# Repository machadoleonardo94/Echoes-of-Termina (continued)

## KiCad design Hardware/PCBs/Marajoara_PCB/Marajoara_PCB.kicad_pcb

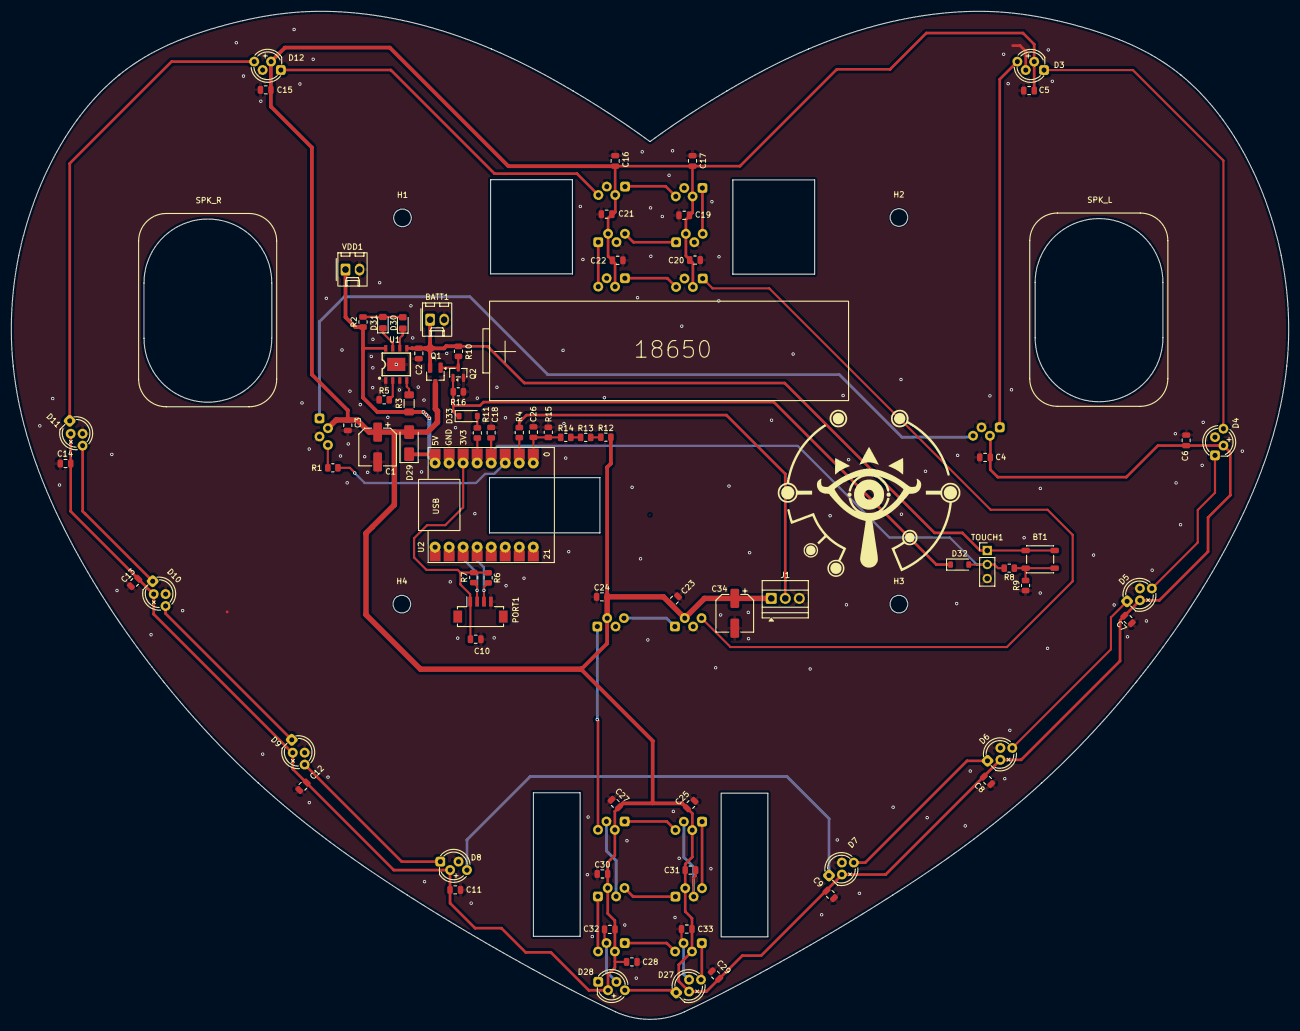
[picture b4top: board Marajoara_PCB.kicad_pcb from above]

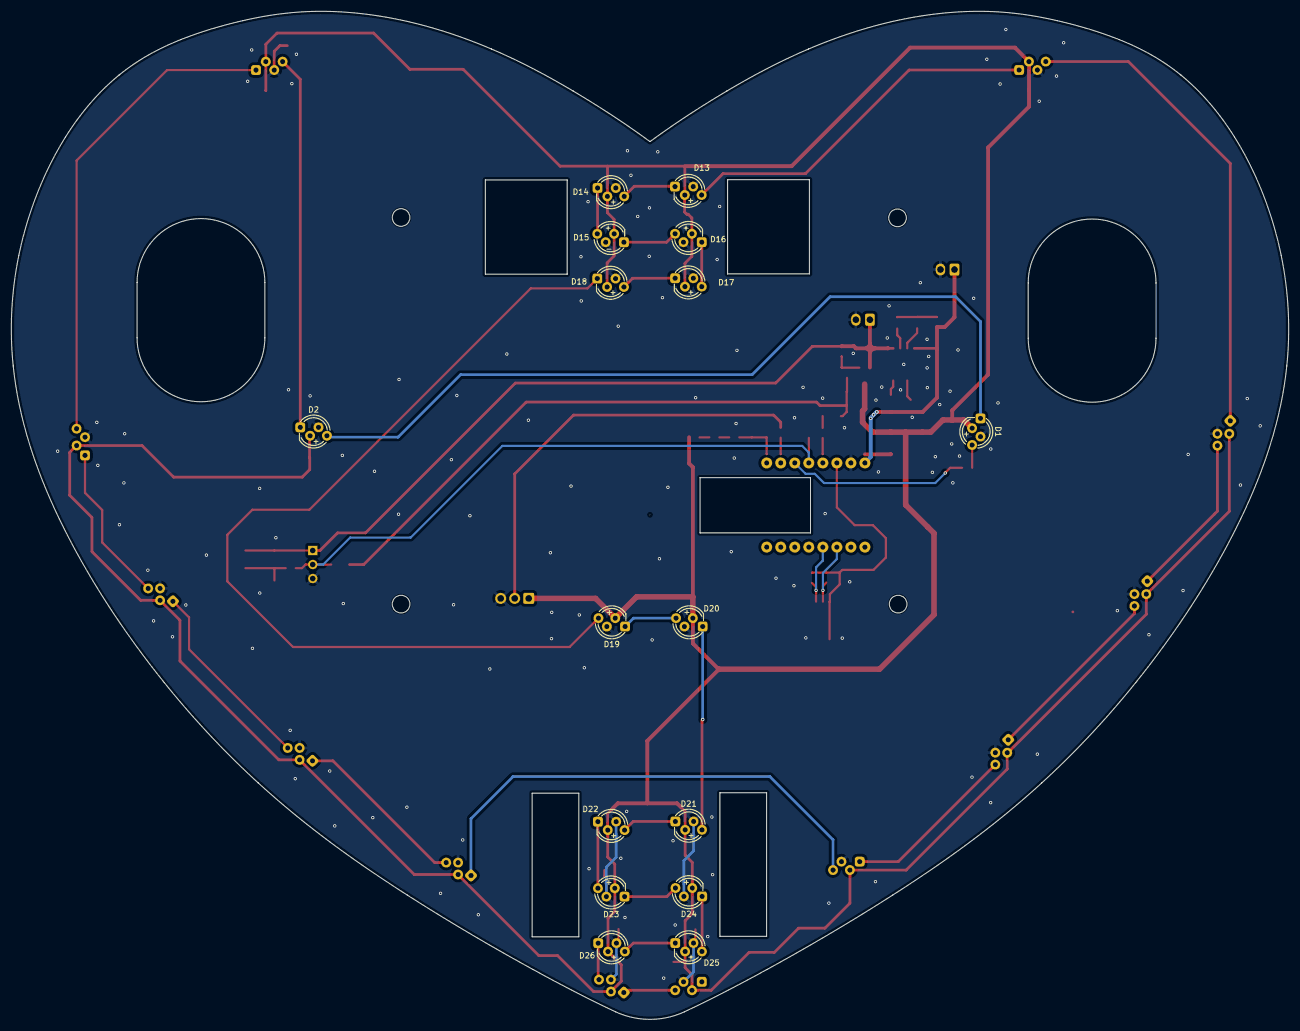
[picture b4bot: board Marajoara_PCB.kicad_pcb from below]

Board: 2 copper layers, 231.3 x 182.5 mm, 99 parts (16 on the bottom side), 52 nets.

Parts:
BATT1: Conn_01x02_Socket; Molex_KK-254_AE-6410-02A_1x02_P2.54mm_Vertical
BT1: SW_Push; SW_SPST_PTS647_Sx38
C1, C34: 220uF; CP_Elec_6.3x7.7
C2, C10: 10u; C_0805_2012Metric
C3, C4, C5, C6, C7, C8, C9, C11, C12, C13, C14, C15, C16, C17, C18, C19, C20, C21, C22, C23, C24, C25, C26, C27, C28, C29, C30, C31, C32, C33: 100nF; C_0805_2012Metric
D1, D2, D3, D4, D5, D6, D7, D8, D9, D10, D11, D12, D13, D14, D15, D16, D17, D18, D19, D20, D21, D22, D23, D24, D25, D26, D27, D28: WS2812B; WS2812B_PTH_staggered
D29: SS14; D_SMA
D30: LED_BLUE; LED_0805_2012Metric_Pad1.15x1.40mm_HandSolder
D31: LED_RED; LED_0805_2012Metric_Pad1.15x1.40mm_HandSolder
D32, D33: 1N4148W; D_SOD-123
H1, H2, H3, H4: MountingHole; MountingHole_3.2mm_M3
J1: Conn_01x03_Socket; TerminalBlock_Xinya_XY308-2.54-3P_1x03_P2.54mm_Horizontal
PORT1: Conn_01x04_Socket; Hirose_DF13C_CL535-0404-8-51_1x04-1MP_P1.25mm_Vertical
Q1: XR5P04; SOT-23_Handsoldering
Q2: 2N7002K; SOT-23
R1, R4, R11: 330; R_0805_2012Metric
R2, R5, R6, R7, R8: 2.2k; R_0805_2012Metric
R3: 220mR 1W 1%; R_1206_3216Metric_Pad1.30x1.75mm_HandSolder
R9, R10, R12, R13, R14, R15: 100k; R_0805_2012Metric
R16: 10k; R_0805_2012Metric
SPK_L: Speaker_4R_3W_35x25mm
SPK_R: Speaker_4R_3W_35x25mm
TOUCH1: Conn_01x03_Socket; PinHeader_1x03_P2.54mm_Vertical
U1: TP4056; ESOP-8_L4.9-W3.9-P1.27-LS6.0-BL-EP
U2: ESP32-C3-Supermini
VDD1: Conn_01x02_Socket; Molex_KK-254_AE-6410-02A_1x02_P2.54mm_Vertical

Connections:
+3.3V: C10.1, PORT1.1, R6.1, R7.1, U2.14 (3V3)
+5V: D29.1 (K), R2.1, R3.1, U1.8 (CE), U2.16 (5V), VDD1.1
+BATT: BATT1.1, BT1.1, C2.1, Q1.2 (S), R10.2, TOUCH1.1, U1.5 (BAT)
ADC1_0: C26.2, R14.1, R15.1, U2.9 (GPIO0)
Button_GPIO: C18.2, D32.2 (A), R8.2, TOUCH1.2, U2.12 (GPIO3)
GND: BATT1.2, C1.2, C2.2, C3.1, C4.1, C5.1, C6.1, C7.1, C8.1, C9.1, C10.2, C11.1, C12.1, C13.1, C14.1, C15.1, C16.1, C17.1, C18.1, C19.1, C20.1, C21.1, C22.1, C23.1, C24.1, C25.1, C26.1, C27.1, C28.1, C29.1, C30.1, C31.1, C32.1, C33.1, C34.2, D1.2 (VSS), D2.2 (VSS), D3.2 (VSS), D4.2 (VSS), D5.2 (VSS), D6.2 (VSS), D7.2 (VSS), D8.2 (VSS), D9.2 (VSS), D10.2 (VSS), D11.2 (VSS), D12.2 (VSS), D13.2 (VSS), D14.2 (VSS), D15.2 (VSS), D16.2 (VSS), D17.2 (VSS), D18.2 (VSS), D19.2 (VSS), D20.2 (VSS), D21.2 (VSS), D22.2 (VSS), D23.2 (VSS), D24.2 (VSS), D25.2 (VSS), D26.2 (VSS), D27.2 (VSS), D28.2 (VSS), J1.3, PORT1.4, Q2.2 (S), R5.1, R9.1, R15.2, R16.2, TOUCH1.3, U1.1 (TEMP), U1.3 (GND), U1.9 (EP), U2.15 (GND), VDD1.2
Majora_out: R1.1, U2.11 (GPIO2)
unnamed: BT1.2, R8.1, R9.2
unnamed: D1.1 (DIN), R1.2
unnamed: D1.4 (DOUT), D2.1 (DIN)
unnamed: D2.4 (DOUT), D3.1 (DIN)
unnamed: D3.4 (DOUT), D4.1 (DIN)
unnamed: D4.4 (DOUT), D5.1 (DIN)
unnamed: D5.4 (DOUT), D6.1 (DIN)
unnamed: D6.4 (DOUT), D7.1 (DIN)
unnamed: D7.4 (DOUT), D8.1 (DIN)
unnamed: D8.4 (DOUT), D9.1 (DIN)
unnamed: D9.4 (DOUT), D10.1 (DIN)
unnamed: D10.4 (DOUT), D11.1 (DIN)
unnamed: D11.4 (DOUT), D12.1 (DIN)
unnamed: D12.4 (DOUT), D13.1 (DIN)
unnamed: D13.4 (DOUT), D14.1 (DIN)
unnamed: D14.4 (DOUT), D15.1 (DIN)
unnamed: D15.4 (DOUT), D16.1 (DIN)
unnamed: D16.4 (DOUT), D17.1 (DIN)
unnamed: D17.4 (DOUT), D18.1 (DIN)
unnamed: D18.4 (DOUT), D19.1 (DIN)
unnamed: D19.4 (DOUT), D20.1 (DIN)
unnamed: D20.4 (DOUT), D21.1 (DIN)
unnamed: D21.4 (DOUT), D22.1 (DIN)
unnamed: D22.4 (DOUT), D23.1 (DIN)
unnamed: D23.4 (DOUT), D24.1 (DIN)
unnamed: D24.4 (DOUT), D25.1 (DIN)
unnamed: D25.4 (DOUT), D26.1 (DIN)
unnamed: D26.4 (DOUT), D27.1 (DIN)
unnamed: D27.4 (DOUT), D28.1 (DIN)
unnamed: D30.2 (A), D31.2 (A), R2.2
unnamed: D30.1 (K), U1.6 (STDBY#)
unnamed: D31.1 (K), U1.7 (CHRG#)
unnamed: D32.1 (K), D33.1 (K), Q2.1 (G), R16.1
unnamed: D33.2 (A), R11.2
unnamed: J1.2, R4.2
unnamed: Q1.1 (G), Q2.3 (D), R10.1
unnamed: R12.1, R13.2
unnamed: R13.1, R14.2
unnamed: R5.2, U1.2 (PROG)
unnamed: R3.2, U1.4 (VCC)
SCL: PORT1.3, R6.2, U2.4 (GPIO8)
SDA: PORT1.2, R7.2, U2.3 (GPIO7)
Strip_out: R4.1, U2.10 (GPIO1)
V_REG: C1.1, C3.2, C4.2, C5.2, C6.2, C7.2, C8.2, C9.2, C11.2, C12.2, C13.2, C14.2, C15.2, C16.2, C17.2, C19.2, C20.2, C21.2, C22.2, C23.2, C24.2, C25.2, C27.2, C28.2, C29.2, C30.2, C31.2, C32.2, C33.2, C34.1, D1.3 (VDD), D2.3 (VDD), D3.3 (VDD), D4.3 (VDD), D5.3 (VDD), D6.3 (VDD), D7.3 (VDD), D8.3 (VDD), D9.3 (VDD), D10.3 (VDD), D11.3 (VDD), D12.3 (VDD), D13.3 (VDD), D14.3 (VDD), D15.3 (VDD), D16.3 (VDD), D17.3 (VDD), D18.3 (VDD), D19.3 (VDD), D20.3 (VDD), D21.3 (VDD), D22.3 (VDD), D23.3 (VDD), D24.3 (VDD), D25.3 (VDD), D26.3 (VDD), D27.3 (VDD), D28.3 (VDD), D29.2 (A), J1.1, Q1.3 (D), R12.2
latch_enable: R11.1, U2.13 (GPIO4)

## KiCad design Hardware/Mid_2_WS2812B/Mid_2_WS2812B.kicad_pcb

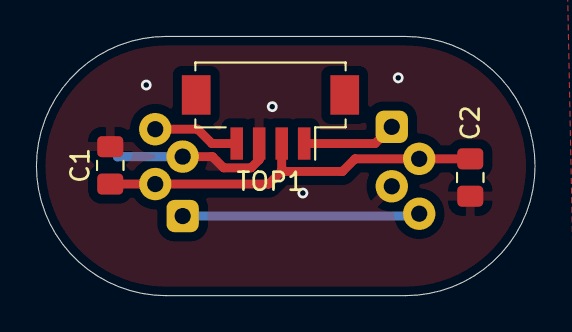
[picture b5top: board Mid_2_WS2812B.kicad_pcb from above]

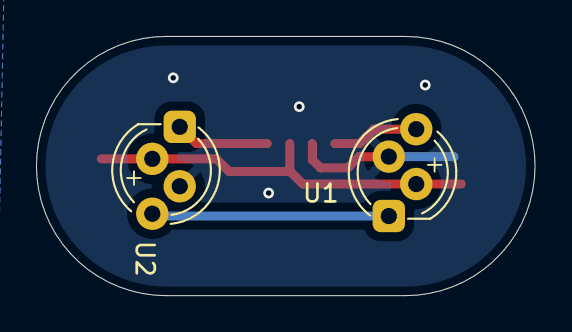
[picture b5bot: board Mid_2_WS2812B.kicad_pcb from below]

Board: 2 copper layers, 27.7 x 14.4 mm, 5 parts (2 on the bottom side), 5 nets.

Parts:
C1, C2: 100n; C_0805_2012Metric_Pad1.18x1.45mm_HandSolder
TOP1: Conn_01x04_Socket; Hirose_DF13C_CL535-0404-8-51_1x04-1MP_P1.25mm_Vertical
U1, U2: WS2812B; WS2812B_PTH_staggered

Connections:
GND: C1.2, C2.2, TOP1.3, U1.2 (VSS), U2.2 (VSS)
unnamed: U1.4 (DOUT), U2.1 (DIN)
Strip_in: TOP1.4, U1.1 (DIN)
Strip_out: TOP1.1, U2.4 (DOUT)
VCC: C1.1, C2.1, TOP1.2, U1.3 (VDD), U2.3 (VDD)

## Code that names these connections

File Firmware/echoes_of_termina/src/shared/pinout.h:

#ifndef PROJECT_GLOBAL_PINOUT
#define PROJECT_GLOBAL_PINOUT

#include "shared/dependencies.h"

//? ------------------------------------------------------------------------------------------
//*! Board pinout selection.
//*!
//*  Pick the board with a build flag in platformio.ini:
//*      -DECHOES_V1      → bench board (default if neither is given)
//*      -DMARAJOARA_V3   → Marajoara_V3
//*!
//*  Both boards carry an ESP32-WROOM-32 N8R2/32UE module, so the board file
//*  cannot imply the pinout — the environment has to state it. Defining both,
//*  or neither, is a hard error rather than a silent fallback onto the wrong
//*  hardware.
//*!
//*  Why compile time and not a runtime variable: the module's 2 MB PSRAM chip is
//*  wired internally to GPIO16 (CS) and GPIO17 (CLK), so whether the external
//*  RAM may be used at all is a property of the pinout, and psramInit() runs
//*  before setup(). PINOUT_PSRAM_AVAILABLE below is what testSPIRAM() in
//*  components/ESP32/setup.h is driven from.
//? ------------------------------------------------------------------------------------------

#if defined(ECHOES_V1) && defined(MARAJOARA_V3)
#error "Define only one board: -DECHOES_V1 or -DMARAJOARA_V3 (see platformio.ini)"
#elif !defined(ECHOES_V1) && !defined(MARAJOARA_V3)
#define ECHOES_V1 // default: the bench board
#endif

#if defined(ECHOES_V1)

// ── Echoes V1 (bench board) ─────────────────────────────────────────────────
#define PINOUT_NAME "Echoes V1"

// The MAX98357A sits on GPIO16/17/18 — the very GPIO16/17 the module's PSRAM
// chip uses for CS/CLK. Driving I2S therefore scrambles every external RAM
// access, so PSRAM must stay disabled on this board (see setup.h testSPIRAM).
#define PINOUT_PSRAM_AVAILABLE 0

//* Outputs:
#define LED_output 25

//* I2S_NUM_0 — MAX98357A speaker via the ESP32-A2DP sink
#define I2C_DOUT 16
#define I2C_BCLK 17
#define I2C_LRC 18

//* I2S_NUM_1 — INMP441 microphone. Wire its L/R pin to GND for the left channel.
#define MIC_SCK 27
#define MIC_WS 26
#define MIC_SD 34

//* microSD — 1-bit (CLK/CMD/D0 only)
#define SDMMC_CLK 14
#define SDMMC_CMD 15
#define SDMMC_D0 2

//* Extras:
#define prog_switch 0
#define button 4
#define latch 13

//* I2C:
#define i2c_sda 21
#define i2c_scl 22

//* Analog input:
#define adc_input 36

#elif defined(MARAJOARA_V3)

// ── Marajoara V3 ────────────────────────────────────────────────────────────
// Pin map taken from the board itself (Marajoara_V3.kicad_pcb, U2 = ESP32-WROOM-32UE
// pad → net). GPIO16 and GPIO17 are NOT broken out on this board, which is what
// makes the 2 MB PSRAM usable here.
#define PINOUT_NAME "Marajoara V3"
#define PINOUT_PSRAM_AVAILABLE 1

//* Outputs:
#define LED_output 23 // net: Strip_out

//* I2S_NUM_0 — MAX98357A speaker, driven by the A2DP sink.
//* The DAC's BCLK and DIN moved onto the SDMMC data nets that the 1-bit microSD
//* no longer needs (IO27 = old SD_D2, IO13 = old SD_D3); LRC stays on 18.
#define I2C_DOUT 13   // net: I2S_SPK_D    (was SD_D3)
#define I2C_BCLK 27   // net: I2S_SPK_BCLK (was SD_D2)
#define I2C_LRC 18    // net: I2S_LRC

//* I2S_NUM_1 — INMP441 microphone, its own peripheral and its own clock pins.
//* None of these clash with PSRAM, so they are unchanged from the original map.
#define MIC_SCK 26    // net: I2S_MIC_BCLK
#define MIC_WS 25     // net: I2S_MIC_WS
#define MIC_SD 34     // net: I2S_MIC_D (input-only pin)

//* microSD — 1-bit. The card only has CLK/CMD/D0/D1 wired to the MCU on this
//* board (no D2/D3), so 4-bit was never an option; D2/D3's nets now carry the
//* DAC's I2S signals.
#define SDMMC_CLK 14
#define SDMMC_CMD 15
#define SDMMC_D0 2

//* Extras:
#define prog_switch 0 // net: PROG
#define button 19     // net: Button_GPIO
#define latch 32      // net: latch_enable (GPIO32 is an RTC GPIO, so the hold works)

//* I2C:
#define i2c_sda 21
#define i2c_scl 22

//* Analog input:
#define adc_input 36 // net: ADC1_0

#endif

// ---------------------------------------------------------------------------
// Pinout invariants
// ---------------------------------------------------------------------------

// The module's PSRAM chip owns GPIO16 (CS) and GPIO17 (CLK). A pinout that
// claims either pin while expecting PSRAM to work will scramble every external
// RAM access — the failure that cost the V1 bring-up several days.
#if PINOUT_PSRAM_AVAILABLE
#if (LED_output == 16) || (LED_output == 17) ||   \
    (I2C_DOUT == 16) || (I2C_DOUT == 17) ||       \
    (I2C_BCLK == 16) || (I2C_BCLK == 17) ||       \
    (I2C_LRC == 16) || (I2C_LRC == 17) ||         \
    (MIC_SCK == 16) || (MIC_SCK == 17) ||         \
    (MIC_WS == 16) || (MIC_WS == 17) ||           \
    (MIC_SD == 16) || (MIC_SD == 17) ||           \
    (SDMMC_CLK == 16) || (SDMMC_CLK == 17) ||     \
    (SDMMC_CMD == 16) || (SDMMC_CMD == 17) ||     \
    (SDMMC_D0 == 16) || (SDMMC_D0 == 17) ||       \
    (prog_switch == 16) || (prog_switch == 17) || \
    (button == 16) || (button == 17) ||           \
    (latch == 16) || (latch == 17) ||             \
    (i2c_sda == 16) || (i2c_sda == 17) ||         \
    (i2c_scl == 16) || (i2c_scl == 17) ||         \
    (adc_input == 16) || (adc_input == 17)
#error "This pinout enables PSRAM but claims GPIO16/GPIO17 (the PSRAM chip's CS/CLK)."
#endif
#endif

#endif // PROJECT_GLOBAL_PINOUT
